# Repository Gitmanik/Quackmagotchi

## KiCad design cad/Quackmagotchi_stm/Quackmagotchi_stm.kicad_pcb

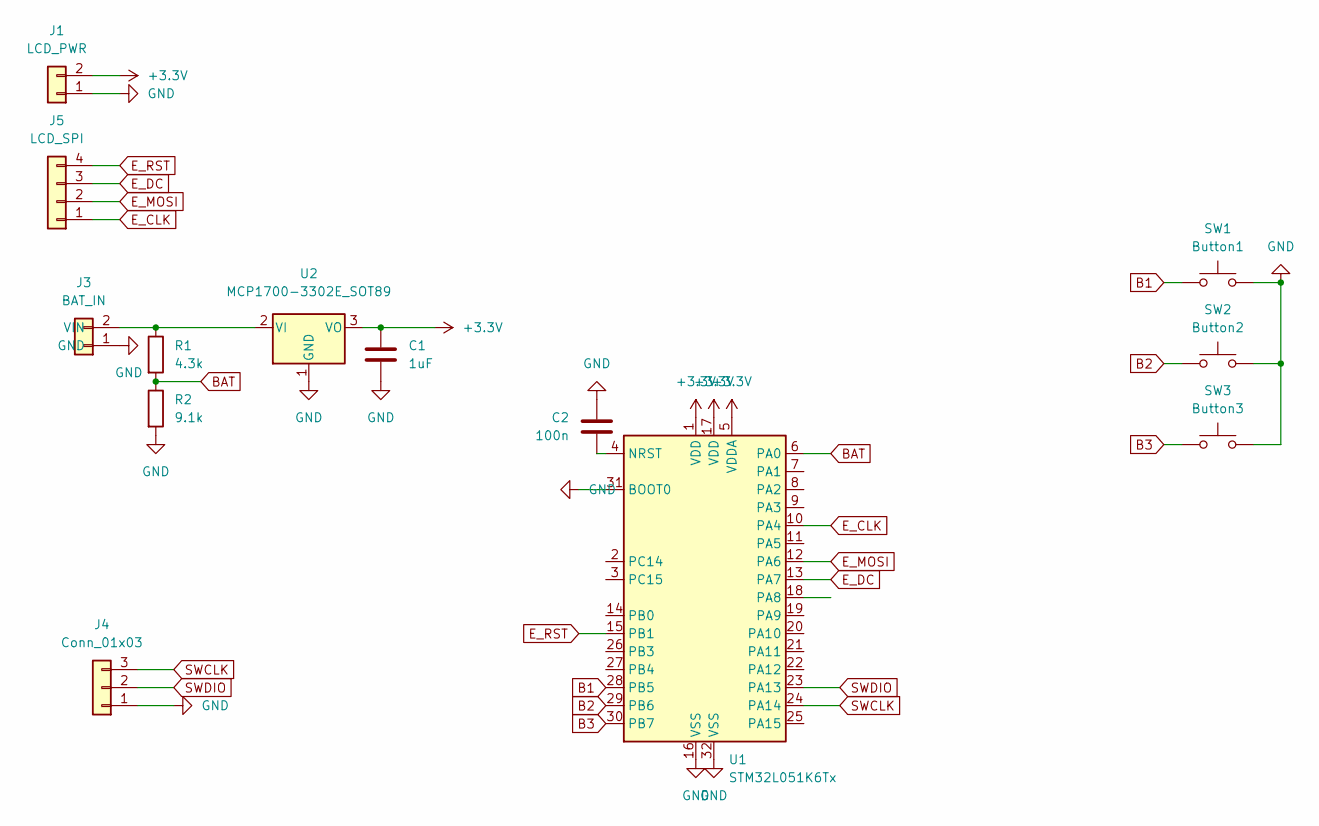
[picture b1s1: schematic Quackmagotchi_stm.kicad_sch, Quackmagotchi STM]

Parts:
C1: 1uF; C_1206_3216Metric_Pad1.33x1.80mm_HandSolder
C2: 100n; C_1206_3216Metric_Pad1.33x1.80mm_HandSolder
J1: LCD_PWR; JST_PH_S2B-PH-K_1x02_P2.00mm_Horizontal
J3: BAT_IN; JST_PH_S2B-PH-K_1x02_P2.00mm_Horizontal
J4: Conn_01x03; PinHeader_1x03_P2.54mm_Vertical
J5: LCD_SPI; JST_PH_S4B-PH-K_1x04_P2.00mm_Horizontal
R1: 4.3k; R_1206_3216Metric_Pad1.30x1.75mm_HandSolder
R2: 9.1k; R_1206_3216Metric_Pad1.30x1.75mm_HandSolder
SW1: Button1; SW_PUSH_6mm_H7.3mm
SW2: Button2; SW_PUSH_6mm_H7.3mm
SW3: Button3; SW_PUSH_6mm_H7.3mm
U1: STM32L051K6Tx; LQFP-32_7x7mm_P0.8mm
U2: MCP1700-3302E_SOT89; SOT-89-3

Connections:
+3V3: C1.1, J1.2, U1.1 (VDD), U1.5 (VDDA), U1.17 (VDD), U2.3 (VO)
B1: SW1.1, U1.28 (PB5)
B2: SW2.1, U1.29 (PB6)
B3: SW3.1, U1.30 (PB7)
BAT: R1.2, R2.1, U1.6 (PA0)
E_CLK: J5.1, U1.10 (PA4)
E_DC: J5.3, U1.13 (PA7)
E_MOSI: J5.2, U1.12 (PA6)
E_RST: J5.4, U1.15 (PB1)
GND: C1.2, C2.1, J1.1, J3.1 (GND), J4.1, R2.2, SW1.2, SW2.2, SW3.2, U1.16 (VSS), U1.31 (BOOT0), U1.32 (VSS), U2.1 (GND)
unnamed: C2.2, U1.4 (NRST)
unnamed: J3.2 (VIN), R1.1, U2.2 (VI)
SWCLK: J4.3, U1.24 (PA14)
SWDIO: J4.2, U1.23 (PA13)

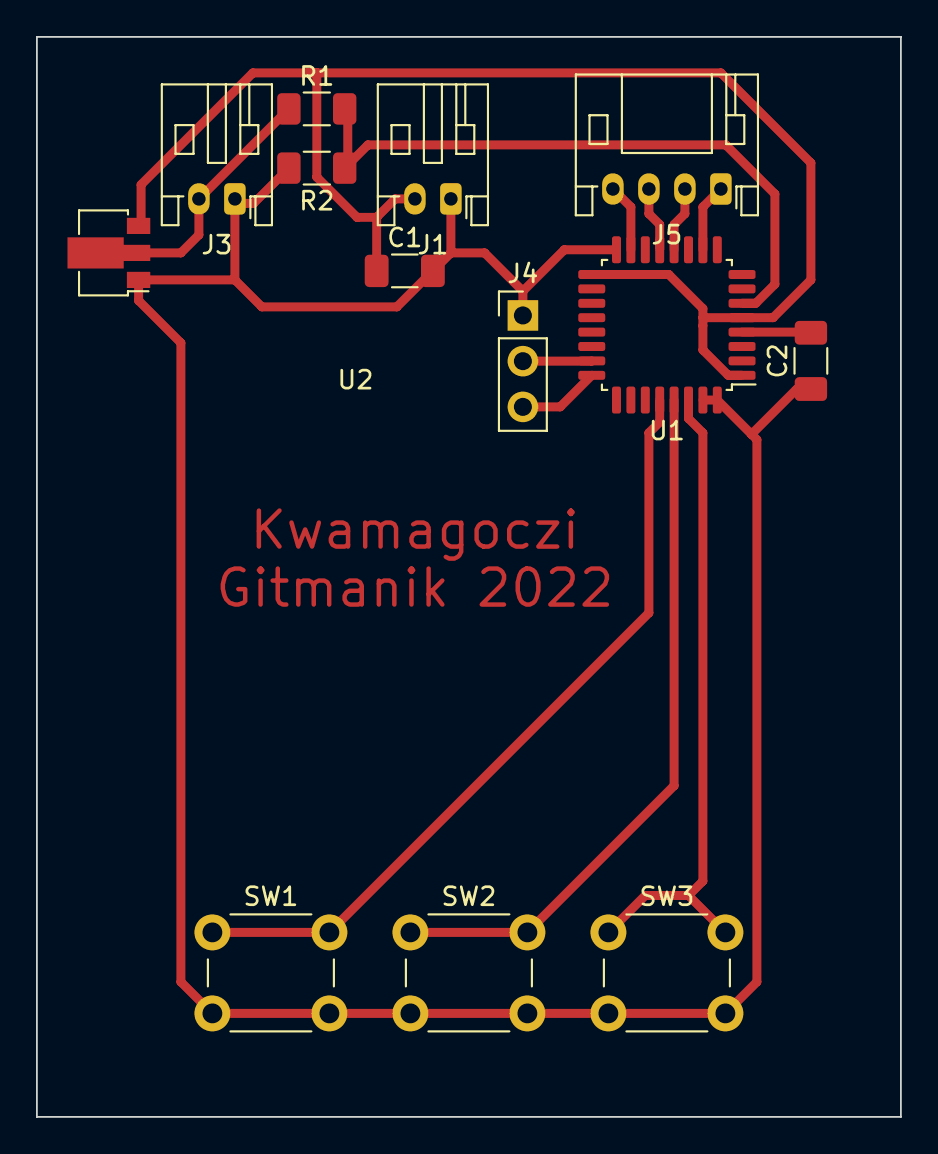
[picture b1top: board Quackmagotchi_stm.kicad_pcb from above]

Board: 2 copper layers, 48.0 x 60.0 mm, 13 parts (0 on the bottom side), 14 nets.

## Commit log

2022-03-05 ten stan
2022-03-06 Kaczka obrazki
2022-03-06 Wylaczenie TIM10, USART2, system stanów
    porzadki, usuwanie zbedych plikow etc
2022-03-14 Duzo zmian, duzo duzo
    font 3x5, map(), menu, wiecej bitmap, izolacja debug screen
2022-03-15 Mozliwosc przerywania animacji, logika przycisków
    Usuniecie bool
2022-03-15 Dalsze oczyszczanie, uint8_t (*func) (), ADC1 In1
2022-03-17 Modularyzacja fontów PCD8544, czyszczenie
2022-03-18 Wyśrodkowanie MENU
2022-03-18 Anulowanie animacji podczas IDLE
2022-03-18 Uproszczenie testowania przycisków
2022-04-18 Włączenie debug USART2, logo w Menu,
2022-04-18 Soft SPI w miejscu hardware`owego, wyłączenie USART2
2022-12-30 Kacze spanie + wiek
2022-12-30 Moved source + Added KiCAD project
